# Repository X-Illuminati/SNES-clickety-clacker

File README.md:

```
     ______     ___   ___   _______     _______   _______
    / ___. \   /  /  /  /  /  ___  \   /  ____/  /  ___  \
   / /   / /  /  /  /  /  /  /  /  /  /  /      /  /  /  /
   | \  /_/  /  /  /  /  /  /  /  /  /  /___   /  /__/  /
  _ \ \     /  /  /  /  /  /__/  /  /  ____/  /      __/
 / / \ \   /  /  /  /  /  _____,'  /  /      /  ___.  \
/ /__/ /  /  /__/  /  /  /        /  /___   /  /   /  /
\_____/   \_______/  /__/        /______/  /__/   /__/

≡≡≡≡≡≡≡≡≡≡≡≡≡≡≡≡≡≡≡≡≡≡≡≡≡≡≡≡≡≡≡≡≡≡≡≡≡≡≡≡≡≡≡≡≡≡≡≡≡≡≡≡≡≡≡≡
#    C  L  I  C  K  E  T  Y  -  C  L  A  C  K  E  R    #
≡≡≡≡≡≡≡≡≡≡≡≡≡≡≡≡≡≡≡≡≡≡≡≡≡≡≡≡≡≡≡≡≡≡≡≡≡≡≡≡≡≡≡≡≡≡≡≡≡≡≡≡≡≡≡≡
    ______    ___     ____    ____     ______    _   __
 __/ ____/___/   |___/  _/_  / __ \   / ____/   / | / /
  / / __  __/ /| |___/ /____/ / / /__/ __/__   /  |/ /
 / /_/ /   / ___ | _/ /  __/ /_/ /__/ /_______/ /|  /__
 \____/   /_/  |_|/___/   /_____/  /_____/   /_/ |_/

                            /\
  /\-----------------------/__\---------------------/\
 /--\                    CONTENTS                  /--\
/`\/`\--------------------------------------------/`\/`\
¯¯¯¯¯¯                                            ¯¯¯¯¯¯
```
- [Introduction](#introduction)
- [Thaumaturgical Design](#thaumaturgical-design)
- [Reagents](#reagents)
- [Crafting Notes](#crafting-notes)
- [Epilogue](#epilogue)

## Introduction

Hail adventurer! I see my little trinket has caught your attention.
If you're interested, I'll tell you all about it. Just pull up a stool and order
your favorite libation. I can vouch for the quality of the ale but be warned:
the bartender is an incurable gossip!

What is it, you ask? Why, it's a SNES controller. Ha! It's barely recognizable
compared to your usual, mundane variety. But, I'll get to that...

Let me tell you why it's useful -- I used to have terrible problems with the
standard SNES controller. After years of adventuring I've developed what the
seven sages call sore-thumb-itosis. Even Morgia root can't treat it once the
disease reaches it's advances stage.  
Well, this sore-thumb-itosis was preventing me from making progress in my
adventures. I couldn't even make it to base camp most of the time.  
But, fortunately, I met a fellow adventurer one evening in an inn much like this
one. He told me that he used to be a great adventurer (until he took an arrow to
the knee), and told me of others he'd met who had a similar problem.
It turns out the issue is fundamental to the design of the stock controller --
the rubber membranes make only intermittent contact and lack any sort of tactile
feedback. This increases fatigue and leads to sore-thumb-itosis.

So I traveled to the far-away court of OSH Park where they produce bespoke
magical artifacts. There I consulted with their renowned thaumaturgists and
artificers and commissioned this bauble -- it employs tactile switch technology
to resolve the deficiencies of the standard controller.  
The artisans that crafted these tactile switches assure me that I could ascend
even to the heights of Mt. Ordeals and still have energy enough to take on an
ancient Balrog or the evil sorcerer Thanatos.  
(I'm not saying I believe any of that, but those gnomes sure have some pretty
good marketing.)

## Thaumaturgical Design

Well, I could go on about this all evening (and probably will if you let me!)
But I've already gotten ahead of myself. We should begin at the beginning --
with the design of the original SNES controller.
The design is fairly basic; a classic shift register. 60 times each second, the
state of the buttons are latched and shifted out, back to the SNES CPU.
The communication protocol is clearly based on a 4021 asynchronous shift
register; the latch signal is not lined up with a clock edge.

Nintendo has gone through a couple of revisions.
Originally, they had 2 8-bit shift registers daisy-chained together.

Latterly, they moved to a simpler layout with a single 16-bit shift register.

The board is a single layer design, but makes use of a separate carbon-film
layer for the button pads and a few jumper tracks.  
There are some signs that they have created a custom shift register rather than
using a standard 4000-series component. The 8-bit shift registers have a
different pinout than the standard 4021. Also, tn both cases above, we can see
that they have omitted a number of important pull-up resistors, choosing to
instead integrate these into the IC, itself.

This was a little concerning, so I went to the trouble of mocking up a 4021
circuit on a breadboard.

It worked properly once the missing pull-ups were added.

My goal in this project was to reuse most of the existing controller.
This meant fitting into the mechanical envelope of the controller housing and
selecting switches that had the proper height to be actuated by the existing
plastic buttons. Another goal was to use all 3 copies of the board received from
OSH Park as a different piece of the overall layout.
[See below](#why-use-osh-park-for-pcb-manufacture) for more details.

The mechanical layout was perhaps the most difficult part with more than half of
the time spent simply rearranging components.

To create the board outline, I scanned in the controller and traced a one-to-one
DXF from the outline. Along with this outline, I also included drill hole
locations and divided the overall board into thirds. I then mirrored this and
created the PCB routing outline from the intersection of the mirrored and
unmirrored copies.

The plastic shell of the controller has several features molded into it that
provide support for the PCB. I wanted to make sure that I didn't put any
components in a position where they would foul against these, so I added several
annotations to some nonfunctional layers in order to mark the keep-out regions.

---
I see you still have questions.  
#### Why not attach switches to the existing controller PCB?
Alas, this would be somewhat impractical. The existing switch contacts are
covered with a carbon film that is difficult to scrape off and many of the
traces are quite thin so that soldering to them would not provide adequately
mechanical anchoring.
However, this was the route chosen for the left and right trigger switches.

#### Why not create new PCBs for the trigger switches?
This PCB is modeled, but OSH Park doesn't support V-scoring so it would have to
be submitted as a separate design.

#### Why use OSH Park for PCB manufacture?
OSH Park is reasonably cheap and fast. Also, their pricing includes 3 copies of
the design and 2 layers, top and bottom. A shrewd buyer can use this to their
advantage!
By mirroring the board layout both sides can be used, one as the left half and
one as the right half, with the 3rd copy as a spare.
Furthermore, the design could be split into thirds with some pads and traces
serving double duty. The layout is a little more effort, but the manufacturing
cost is reduced by about 50%.

#### How do you test such a complicated design?
It mostly depends on getting things right in the schematic, then the layout
tool will do most of the work for you. When using pads and tracks for multiple
purposes they have to be shown that way in the schematic. Sometimes this
involves extra care to separate power and ground. In other cases it just means
creating a more descriptive label for the net to avoid confusion.
Still, it is easy to get messed up when going through board-to-board jumper
connections or when using two legs of a switch to jump over some other tracks.
To check for this, I made a simple cardboard mockup and highlighted the traces
as I reviewed the path for each signal in the layout.

#### What about those capacitors?
The value was not chosen very scientifically. A review of typical application
circuits indicated a value of 0.1 or 0.01 µF. This is a fairly low speed
application, so the value is probably not critical and I just chose 0.1 µF
arbitrarily.
Those who are concerned with it might follow the methodology in
[this Youtube video](https://www.youtube.com/watch?v=9EaTdc2mr34)
from Alan Wolke (w2aew).

## Reagents

So, you're thinking you might build one for yourself, aye?
It can be done by any experienced thaumaturgist and the fine folks of OSH Park
will be happy to oblige by replicating the design.

So what about the remaining reagents?
None of them are particularly uncommon, so you won't need to fight your way to
the top of Darm Tower to get what you need. Just seek out the nearest outfitter,
guild shop, or magical supply.
I recommend The Sharper Mage in Lycaeum or, failing that, DigiKey.

Here's a list of what you'll need:

### Core Components
* [2x] 4021 8-bit asynchronous shift register in SOIC-16 package
* [2x] ceramic capacitor in 1206 SMD package
  * Exact value is not particularly important
  * Recommend 0.01 µF - 10 µF
* [14x] pull-up resistors in 1206 SMD package
  * Exact value is not particularly important
  * Recommend 10 kΩ - 100 kΩ
* [4x] D-Pad switches (3.8 mm actuator height, Gullwing SMD package)
  * Tactile pushbutton, SPST-NO
  * Recommend comparing exact dimensions to the [KSC datasheet](doc/README.md)
* [4x] ABXY switches (4.3 mm actuator height, Gullwing SMD package)
  * Tactile pushbutton, SPST-NO
  * Recommend comparing exact dimensions to the [KSC datasheet](doc/README.md)
* [10x] Wire Links for Board-to-Board Wiring
  * 0.1 in. (2.54mm) spacing

### Optional Components
* [2x] L/R Trigger switches (7.7 mm actuator height, Gullwing SMD package)
  * Optional, not included in OSH Park-optimized design
  * Tactile pushbutton, SPST-NO
  * Recommend comparing exact dimensions to the [KSC datasheet](doc/README.md)
* [2x] 2-pin headers for trigger boards, 0.1 in. (2.54 mm) spacing
* [2x] 2-pin housing for trigger board wires, 0.1 in. (2.54 mm) spacing
* [1x] 5-pin header for CN1, 0.1 in. (2.54 mm) spacing
* [1x] 5-pin housing for CN1 cable, 0.1 in. (2.54 mm) spacing
* [9x] 0.1 in. (2.54 mm) wire crimps

If you're looking for specific recommendations or need help with DigiKey's
telepathic ordering system, try these mantras:

### Links for Core Components
* [2x] [ON Semi mc14021b](https://www.digikey.com/short/3wn7b8)
* [2x] [0.1 µF 1206 SMD ceramic capacitor](https://www.digikey.com/short/3wn7bm)
* [14x] [47 kΩ 1206 SMD resistor](https://www.digikey.com/short/3wn75j)
* [4x] D-Pad switch
  * No good recommendation yet
  * Pads are set up for [C&K KSC201GLFS](https://www.digikey.com/short/3wn7bn).
    However, this switch does not have a tall enough actuator and has too tall
    of a switch body.
  * The [Bourns 7914H](https://www.digikey.com/short/3nt825) works acceptably
    but doesn't fit the pads and doesn't have a great feel, either.
  * [This search](https://www.digikey.com/short/3nt8n5) may be helpful.
* [4x] [C&K KSC701GLFS](https://www.digikey.com/short/3wn7b0)

### Links for Optional Components
* [2x] [C&K KSC621GLFS](https://www.digikey.com/short/3wn7b1)
* [2x] [2-pin header](https://www.digikey.com/short/3wn728)
* [2x] [2-pin housing](https://www.digikey.com/short/3wn7d8)
* [1x] [5-pin header](https://www.digikey.com/short/3wn7d2)
* [1x] [5-pin housing](https://www.digikey.com/short/3wn7d0)
* [9x] [0.1 in. wire crimps](https://www.digikey.com/short/3wn7vh)

## Crafting Notes

Once you've acquired your reagents and the blank PCB from OSH Park, you can
begin the assembly process.  
Start by inspecting the PCBs.

You'll want to make note of any defects. In this design each board has an
unused side (or mostly unused), so you can use just the good side of each board
if there are defects.

Some cleanup of the board edge will be necessary. The mousebites from the
panelization will need to be trimmed off and a lite sanding of the edges could
be helpful.  
You can also test the mechanical fit by placing the boards in the controller
housing.

It is a good strategy to prep your workspace; you will want to avoid any
interruptions in your incantations.  

(Note: soldering iron off-screen.)

The small parts involved can be tricky to work with; I recommend taping the
strips of parts to your work surface to avoid getting scattered by any chance
breeze. And definitely clear the area of any small children or animals.
(Luckily, DigiKey anticipates this need and includes a free cat toy with every
order!)

Here, I've placed all of the front side parts:

And a closeup:

(Note: the right-angle header on CN1 needs to face the other direction.)

The middle section is a little bit special in that it has parts on the back as
well.

The next step is to link the boards together. I found it easiest to assemble
them in the controller housing and tack down the jumper links.

(Note: the right-angle header on CN1 needs to face the other direction.)

The jumper links are very small and can be difficult to solder without bridging.
If you have problems, remember to apply lots of flux and use a fine tip on your
soldering iron so you can heat up the pad and just a single link.  
Use a multimeter continuity test to ensure none of the links are shorted.
It can also be good to test end to end continuity between ground and the input
pin on the IC (when the appropriate button is pressed).

Once this is finished, there remains a few details to take care of.  
An optional step is to put tactile switches on the trigger boards.
This can be done by scraping off the solder mask over the two traces and tacking
either side of the switch to them.

Some form of glue is probably necessary, but hot-melt glue doesn't really work
very well. Probably, a two-part epoxy is recommended.

Connect the trigger boards to P11 and P13. I had to add longer wires for this.

Another issue comes up with the choice of switches for the D-Pad and a couple
of issues with the plastic D-Pad button disc.  
The D-Pad needs a fair amount of clearance around above the switch body or it
will foul against it and fail to actuate the switch. The switch needs to be
between 3.7 mm and 4 mm. 3.8 mm is probably ideal, but might not work if the
switch body is really tall.  
You might be able to carve out some extra clearance in your D-Pad disc:

Note that it is very difficult to do this with a utility knife and impossible
without cutting yourself.  
In the image above, I just covered the slots with tape, which sort of works.
It would be better to fill the slots with epoxy so that the actuator of the
tactile switch doesn't slip up into it.

Here is the fully assembled controller:

And an action shot!

## Epilogue

Well, my mug's nearly empty now, and Trammel is high in the sky.
Perhaps tomorrow will bring renewed invigoration and I'll make some improvements
to the design or add some tips for future adventurers.  
There's plenty of work left to do.
1. Improvements to the layout
   * general routing improvements
     * route ground path around the outside of the board
     * route +5 V down center
     * route the bottom side traces predominantly vertical
     * route the top side traces predominantly horizontal
     * rotate U1 180°
     * rotate U2 180° or, possibly, 90° CCW
2. Create DIP package variant
(or perhaps support both DIP and SMT in one design).
3. Create 3D-printable models for select/start button caps

Copywrite © 2017 Chris Baker.
[CC-BY-4.0](https://creativecommons.org/licenses/by/4.0/)
See [LICENSE.txt](LICENSE.txt) for details.

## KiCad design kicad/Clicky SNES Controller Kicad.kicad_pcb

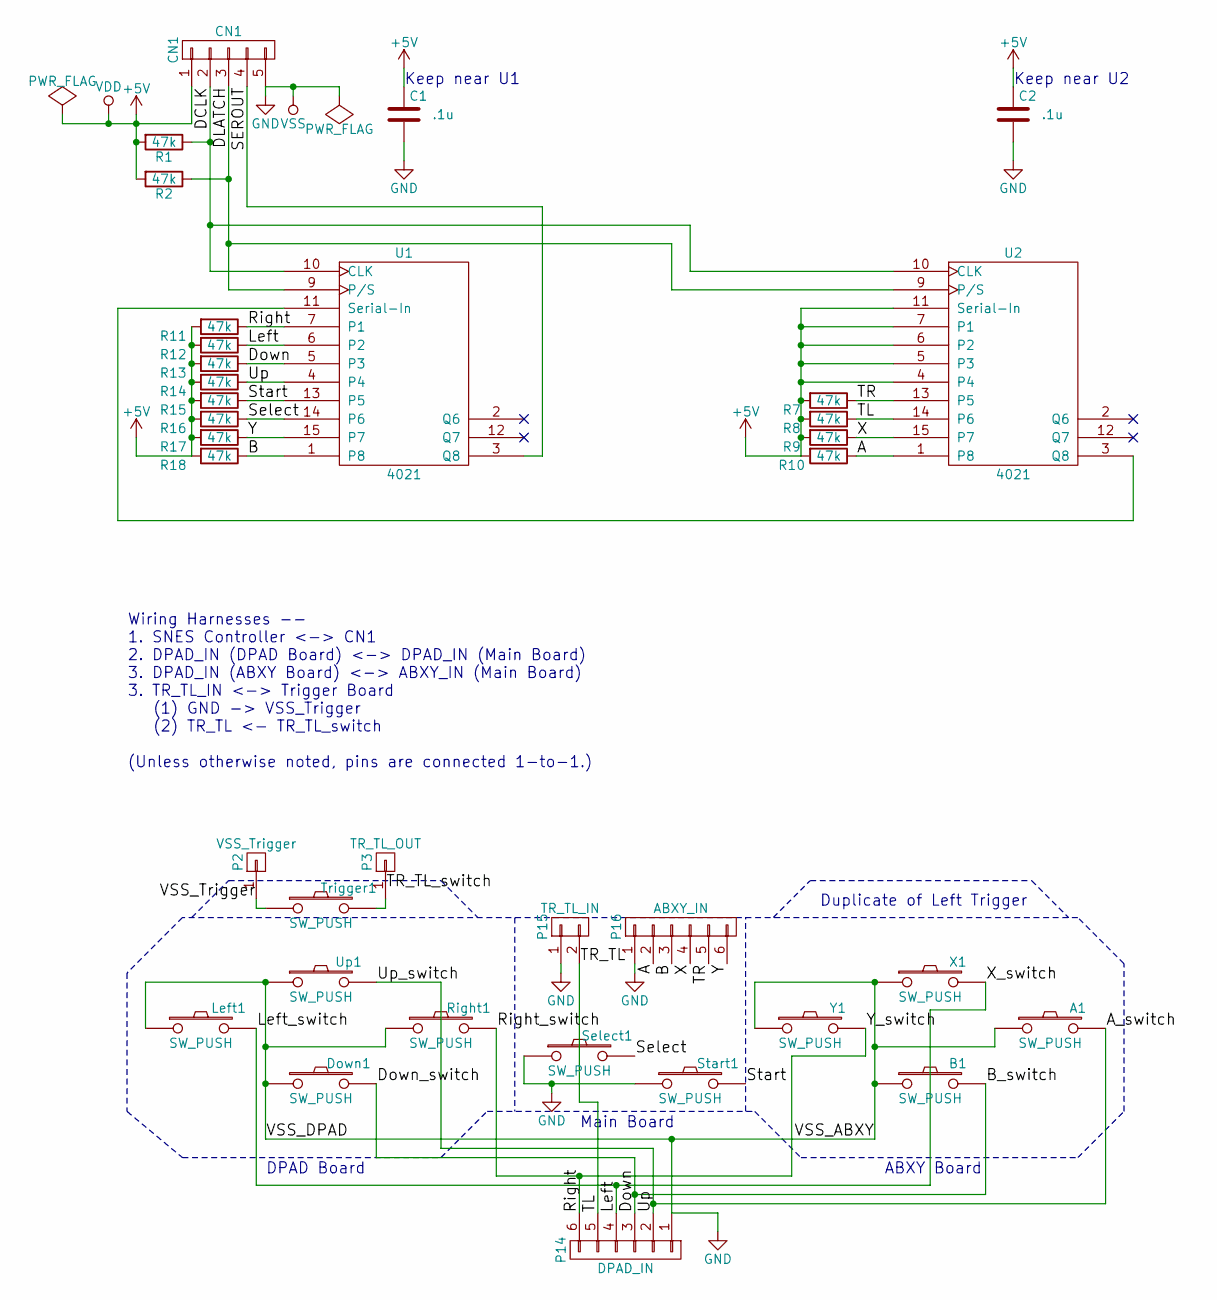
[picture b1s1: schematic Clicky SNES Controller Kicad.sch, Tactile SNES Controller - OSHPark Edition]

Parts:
A1: SW_PUSH; SW_SPST_KSC7-G
B1: SW_PUSH; SW_SPST_KSC7-G
C1, C2: .1u; C_1206
CN1: CN1; Pin_Header_Angled_1x05_Pitch2.54mm_Sinister
Down1: SW_PUSH; SW_SPST_KSC2-G
Left1: SW_PUSH; SW_SPST_KSC2-G
P2: VSS_Trigger; Pin_Header_Straight_1x01_Pitch2.54mm
P3: TR_TL_OUT; Pin_Header_Straight_1x01_Pitch2.54mm
P14: DPAD_IN; Pin_Header_Straight_1x06_Pitch2.54mm
P15: TR_TL_IN; Pin_Header_Straight_1x02_Pitch2.54mm
P16: ABXY_IN; Pin_Header_Straight_1x06_Pitch2.54mm
R1, R2, R7, R8, R9, R10, R11, R12, R13, R14, R15, R16, R17, R18: 47k; R_1206
Right1: SW_PUSH; SW_SPST_KSC2-G
Select1: SW_PUSH; SW_SPST_Plated_Pad_5.5mm
Start1: SW_PUSH; SW_SPST_Plated_Pad_5.5mm
Trigger1: SW_PUSH; SW_SPST_KSC6-G
U1, U2: 4021; SOIC-16_3.9x9.9mm_Pitch1.27mm
Up1: SW_PUSH; SW_SPST_KSC2-G
X1: SW_PUSH; SW_SPST_KSC7-G
Y1: SW_PUSH; SW_SPST_KSC7-G

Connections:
+5V: C1.1, C2.1, CN1.1, R1.2, R2.2, R7.2, R8.2, R9.2, R10.2, R11.2, R12.2, R13.2, R14.2, R15.2, R16.2, R17.2, R18.2, U1.16 (VDD), U2.4, U2.5 (P3), U2.6 (P2), U2.7 (P1), U2.11 (Serial-In), U2.16 (VDD)
/A: P16.2, R10.1, U2.1 (P8)
/A_switch: A1.2, P14.2, R14.1, U1.4, Up1.2
/B: P16.3, R18.1, U1.1 (P8)
/B_switch: B1.2, Down1.2, P14.3, R13.1, U1.5 (P3)
/DCLK: CN1.2, R1.1, U1.10 (CLK), U2.10 (CLK)
/DLATCH: CN1.3, R2.1, U1.9 (P/S), U2.9 (P/S)
/Left: Left1.2, P14.4, R12.1, U1.6 (P2), X1.2
/Right: P14.6, R11.1, Right1.2, U1.7 (P1), Y1.2
/SEROUT: CN1.4, U1.3 (Q8)
/Select: R16.1, Select1.2, U1.14 (P6)
/Start: R15.1, Start1.2, U1.13 (P5)
/TL: P14.5, P15.2, R8.1, U2.14 (P6)
/TR: P16.5, R7.1, U2.13 (P5)
/VSS_Trigger: P2.1, Trigger1.1
/X: P16.4, R9.1, U2.15 (P7)
/Y: P16.6, R17.1, U1.15 (P7)
GND: A1.1, B1.1, C1.2, C2.2, CN1.5, Down1.1, Left1.1, P14.1, P15.1, P16.1, Right1.1, Select1.1, Start1.1, U1.8 (VSS), U2.8 (VSS), Up1.1, X1.1, Y1.1
unnamed: P3.1, Trigger1.2
unnamed: U1.11 (Serial-In), U2.3 (Q8)

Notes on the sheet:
Duplicate of Left Trigger
Wiring Harnesses -- 1. SNES Controller <-> CN1 2. DPAD_IN (DPAD Board) <-> DPAD_IN (Main Board) 3. DPAD_IN (ABXY Board) <-> ABXY_IN (Main Board) 3. TR_TL_IN <-> Trigger Board (1) GND -> VSS_Trigger (2) TR_TL <- TR_TL_switch (Unless otherwise noted, pins are connected 1-to-1.)
Keep near U1
Keep near U2
Main Board
DPAD Board
ABXY Board

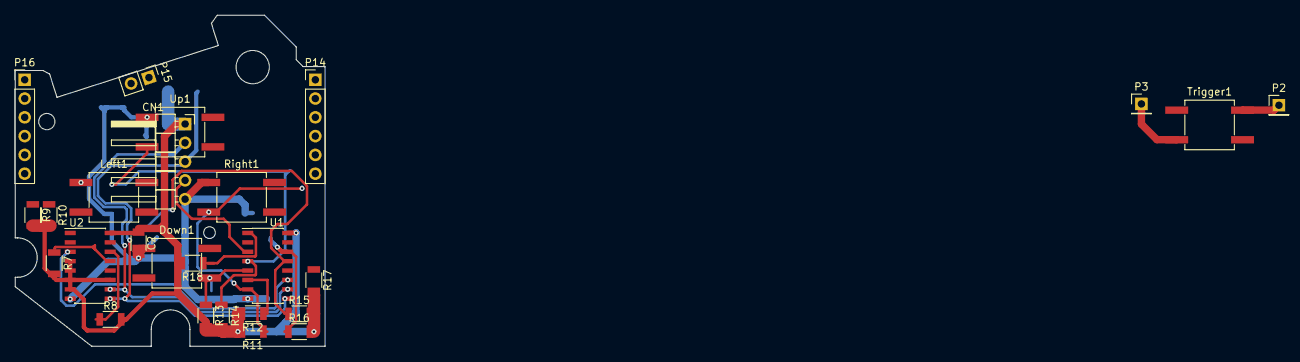
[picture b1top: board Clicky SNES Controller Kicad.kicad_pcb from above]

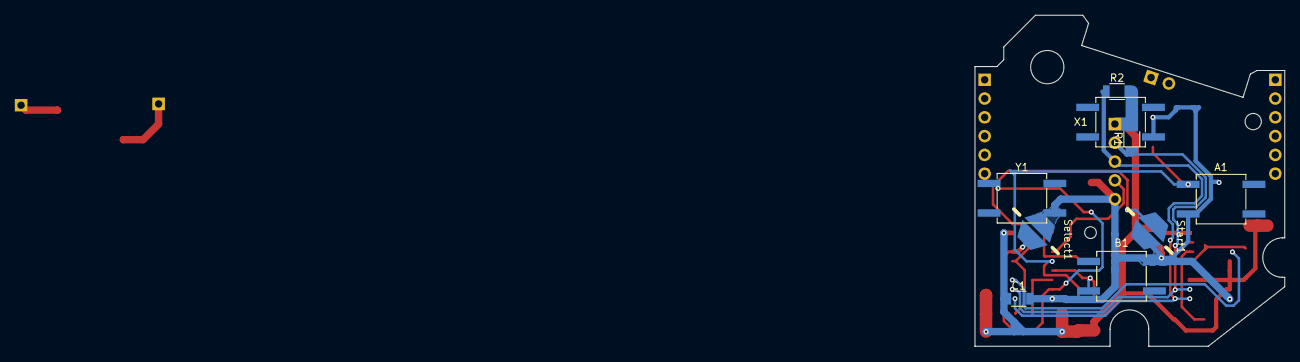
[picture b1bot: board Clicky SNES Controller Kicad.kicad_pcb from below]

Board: 2 copper layers, 41.9 x 44.8 mm, 35 parts (9 on the bottom side), 20 nets.

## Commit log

2017-02-21 Initial schematic and documentation
2017-02-21 Schematic Rev 2 - Reduce connector count
    -refactor the design to reduce the amount of board-to-board wires
    -label board-to-board connectors
    -add board-to-board wiring documentation
    -split voltage domains between the two shift registers (creating 2 new
    parts in the project cache lib)
    -move custom cmos4000 lib out of the project directory
2017-02-26 PCB Rev 1: Create basic board outline
    Scanned in the original circuit board and imported the vector drawing.
    Roughed-out the board outline so that buttons will be in relatively
    the correct place and board will fit within the existing plastic
    envelope of the controller.
2017-02-26 Add PCB backup file to gitignore
2017-02-26 Add scans of original controller PCB
2017-02-26 Add vectorized DXF versions of original PCB outline
2017-03-18 Add some dimension annotations to user notes layer
2017-03-18 Add scanned notes about original circuit board
2017-03-18 Add FreeCAD project files for the DXF PCB outlines
    I'm not sure this is the best way to control FreeCAD documents.
    These particular files probably won't change much over time, though.
2017-03-19 Add SOIC-16 package footprint to the shift registers
2017-03-19 Change project to look for custom libs on BOXY
2017-03-19 Update footprint associations for the switches
    Added custom footprints for all the switches.
2017-03-19 Set up OSH Park design rules
2017-03-19 Restart PCB with OSH Park blank template
2017-03-19 PCB Rev 2: Create basic board outline
    Re-imported the vector drawing of the mechanical board outline and put
    the mirrored copy on a different layer so it can be differentiated by
    color.
    Eco1.User is the unmirrored drawing.
    Eco2.User is the mirrored drawing
    Added some mechanical keep-out areas to these layers as well.
2017-03-19 PCB Rev 2: Add mounting holes
    Added some drill holes to the main board.
    Still need to figure out the final position for the hole on the start /
    select board, but a placeholder is in the file for now.
2017-03-19 netlist: Update footprint associations
2017-03-20 SCH/NET: Attempt to fix issue with VDD/VSS labels on headers
    CN1 pin 1 was routed incorrectly and not labeled as VDD.
    Some of the other connectors don't have proper association with local
    VDD/VSS, nor do U1 and U2.
    This change mostly fixes it, but U1 is still showing raw VDD/VSS
    instead of the board-local VDD/VSS.
2017-03-20 PCB: Import netlist and arrange large components
    This is a first pass at laying out the components.
    There is definitely a problem with the netlist, though.
    Many of the connectors are showing that they only have 1 pin instead of
    2 or 3.
2017-03-20 PCB: Update start/select button footprint
    Fixed a problem in the library with the soldermask covering these pads.
2017-03-25 Fix KiCad Project library paths
    I moved the custom library path to a subdirectory called "library"
    when I added the custom footprint and 3D models to that project.
2017-03-25 Schematic Rev 3 - Rework board-to-board jumpers
    Decided to go with 3 full size boards to fill the mechanical space in
    the controller instead of using the 3rd board as a spare.
    This allows to move CN1 and both ICs onto the center board, which now
    has plenty of space.
    This solves several problems working around plastic ridges behind the
    boards where I wanted to place components and reduces the number of
2017-03-26 Change footprint for trigger connectors
    Change these to use .1" headers in case I want to add connectors
    later so that I can swap the trigger boards.
2017-03-26 PCB: Update start/select button footprint
2017-03-26 PCB Rev 3: Import updated netlist
    Many components removed/updated so complex netlist import.
    Had to lock some manually placed pads (mounting holes).
    Added some additional keep-out regions for the main board:
    - There is cross on the top side of the main board
    - There is a ring behind the select/start buttons on the main board
    - I put these keep-outs on the Cmts.User layer
2017-03-26 SCH/NET: Remove extra pullup, Rename CN1 PCB: Imported new netlist, Arranged resistors in order
2017-03-26 PCB: Place passive components
2017-03-26 Add _autosave files to .gitignore
2017-03-26 Add title and revision to workshet notes
2017-03-26 PCB: Update custom trace widths
    Custmo values (sizes in mm):
    0.1524 - minimum trace size
    0.35 - SOIC-16 leg width
    0.58 - SOIC-16 pad width
    0.635 - .1" header pin width
    0.65 - gull-wing switch leg width
2017-03-26 PCB: Route back side of board
    This is the simpler side of the board, but getting a basic layout
    in place will help when routing the top side as I will know where
    I can drop a via through to jump over other tracks.
2017-03-26 PCB: Minor optimization for back-side
    Noticed a missing GND route.
    Moved the DLATCH pullup resistor in order to facilitate some better
    pathing for the A_switch and GND nets.
2017-03-26 PCB: Add power tracks to top layer
2017-03-26 PCB: Move C2 to reduce GND loop area with U2
2017-03-26 PCB: Finish routing passives
    Had to fuss with the +5V route and placement of some of the
    resistors to get this to work out reasonably well.
2017-03-26 PCB: Route remaining Clock, Latch, and Serout nets
2017-03-26 PCB: Route ABXY_IN pins
2017-03-27 PCB: Route TR/TL jumper pins
2017-03-27 PCB: Route DPAD_IN pins
2017-03-27 PCB: Move TR/TL Connectors to avoid fouling on CN1
    These connectors were also swapped to the wrong side of the board
    which is partly why I didn't notice the mechanical collision.
    I'm debating whether they need to actually be moved to the DPAD
    and ABXY boards, but that is a pretty big tear up.
    Anyway, I took the opportunity to optimize some of the GND routing.
2017-03-27 Change color of F.Fab and B.Fab layer
    I guess this might just be a noop if the layer colors are stored in
    the general/global user preferences instead of in the project.
2017-03-27 PCB: Fix some DRC errors
2017-04-02 Cleanup for OSH Park submission
    Deleted the extra LR Trigger board.
    Deleted a bunch of extra graphic lines on user comment layers.
2017-04-02 Move images to doc directory
2017-04-03 Documentation cleanup
    Used git filter-branch to remove copywrited documentation in preparation
    for uploading to github.
    Added a README to explain this and point to alternate sources of the
    documentation files.
2017-04-03 Update doc/README.md formatting
    GitHub puts the bullet points all on the same line, so add some code tags to make this more visually distinct.
2017-04-03 Update doc/README.md formatting
    Previous commit was borked
2017-04-23 Add documentation images
2017-04-27 Add more documentation images
2017-04-28 Add readme and license
2017-06-04 change pads on passives to non hand-soldering versions
2017-06-04 Rotate CN1 180° to fix silkscreen marking
    Instead of rotating this and having to renumber all of the pins
    I created a new footprint that was mirror-imaged to be left-facing.
2017-06-04 Route TR/TL through the board-to-board connectors
    Having TR and TL connectors on the main board puts them too far
    away from the trigger boards. This prevents the existing wires
    on those boards from being reused.
    Move the connectors to the center of the top edge of the ABXY
    and DPAD boards (a single connector can be used on both boards).
    This combines P11 and P13 (now P15).
